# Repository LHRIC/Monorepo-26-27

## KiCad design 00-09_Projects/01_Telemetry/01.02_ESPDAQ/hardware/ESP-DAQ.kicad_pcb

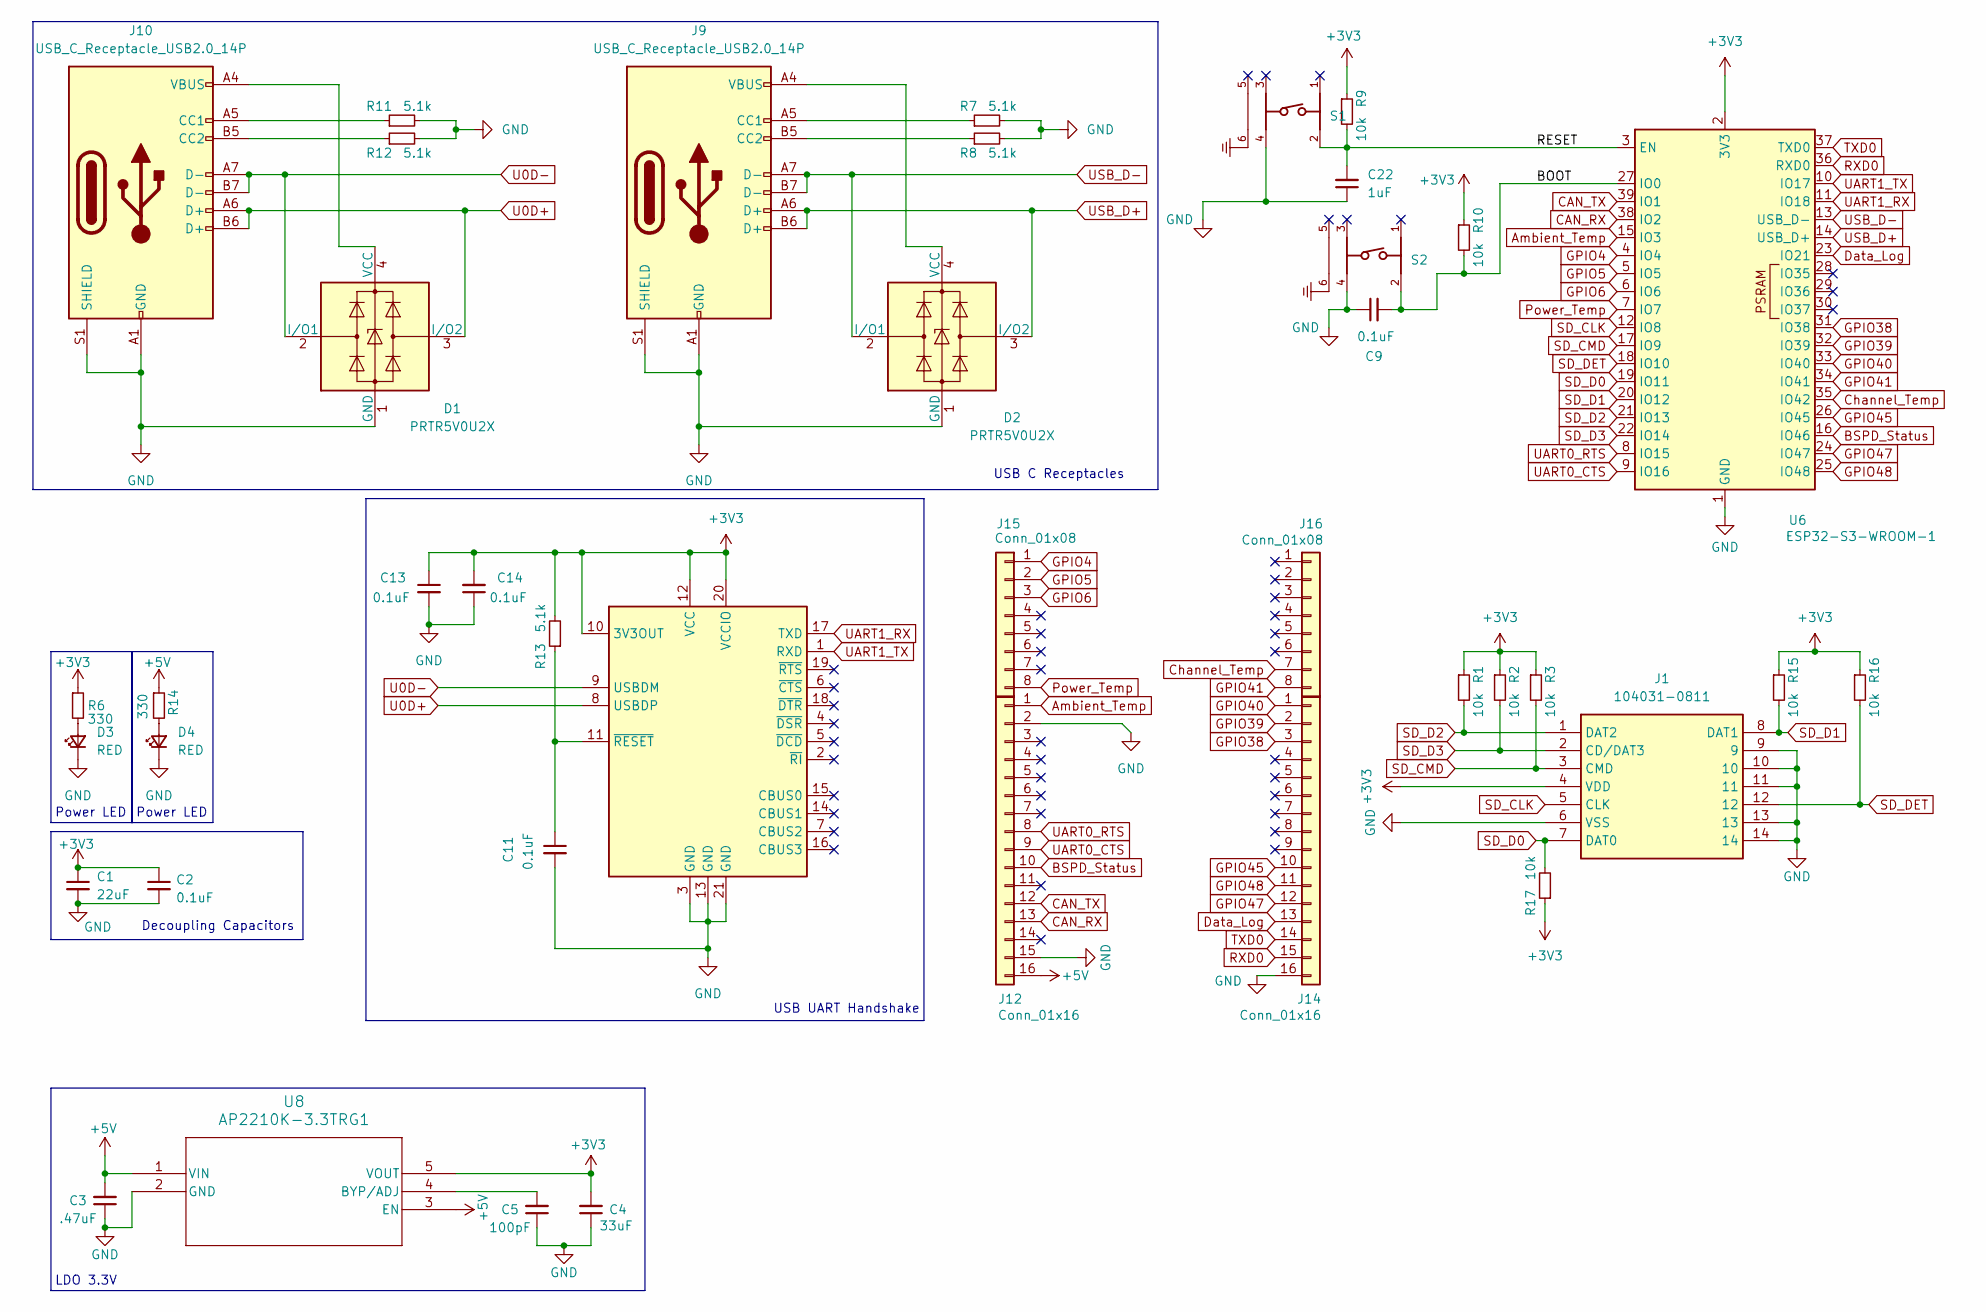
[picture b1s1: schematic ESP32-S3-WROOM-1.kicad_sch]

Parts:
C1: 22uF; C_0805_2012Metric
C2, C9, C11, C13, C14: 0.1uF; C_0603_1608Metric
C3: .47uF; C_0603_1608Metric
C4: 33uF; C_0805_2012Metric
C5: 100pF; C_0603_1608Metric
C22: 1uF; C_0603_1608Metric
D1, D2: PRTR5V0U2X; SOT-143
D3, D4: RED; LED_0603_1608Metric
J1: 104031-0811; Molex MicroSD Card 1040310811; Mouser Part Number 538-104031-0811
J9, J10: USB_C_Receptacle_USB2.0_14P; USB_C_Receptacle_XKB_U262-16XN-4BVC11
J12, J14: Conn_01x16; PinHeader_1x16_P2.54mm_Vertical
J15: Conn_01x08; 01x08 2.54mm Connector Surface Mount Right Angle Left
J16: Conn_01x08; 01x08 2.54mm Connector Surface Mount Right Angle Right
R1, R2, R3, R9, R10, R15, R16, R17: 10k; R_0603_1608Metric
R6, R14: 330; R_0603_1608Metric
R7, R8, R11, R12, R13: 5.1k; R_0603_1608Metric
S1, S2: 435171014816; SMT Switch 435171014816; DigiKey_Part_Number 732-435171014816CT-ND
U1: FT231XQ; QFN-20-1EP_4x4mm_P0.5mm_EP2.5x2.5mm
U6: ESP32-S3-WROOM-1; ESP32S3-WROOM-1U-N16R8
U8: AP2210K-3.3TRG1; SOT-23-5_DIO

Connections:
+3V3: C1.1, C2.1, C4.2, C13.1, C14.2, J1.4 (VDD), R1.1, R2.1, R3.1, R6.1, R9.1, R10.1, R13.2, R15.1, R16.1, R17.1, U1.10 (3V3OUT), U1.12 (VCC), U1.20 (VCCIO), U6.2 (3V3), U8.5 (VOUT)
+5V: C3.2, J12.16, R14.1, U8.1 (VIN), U8.3 (EN)
/BOOT: C9.2, R10.2, S2.2, U6.27 (IO0)
/RESET: C22.2, R9.2, S1.2, U6.3 (EN)
Ambient_Temp: J12.1, U6.15 (IO3)
BSPD_Status: J12.10, U6.16 (IO46)
CAN_RX: J12.13, U6.38 (IO2)
CAN_TX: J12.12, U6.39 (IO1)
Channel_Temp: J16.7, U6.35 (IO42)
Data_Log: J14.13, U6.23 (IO21)
GND: C1.2, C2.2, C3.1, C4.1, C5.1, C9.1, C11.2, C13.2, C14.1, C22.1, D1.1 (GND), D2.1 (GND), D3.1 (K), D4.1 (K), J1.6 (VSS), J1.9, J1.10, J1.11, J1.13, J1.14, J9.A1 (GND), J9.A12 (GND), J9.B1 (GND), J9.B12 (GND), J9.S1 (SHIELD), J10.A1 (GND), J10.A12 (GND), J10.B1 (GND), J10.B12 (GND), J10.S1 (SHIELD), J12.2, J12.15, J14.16, R7.2, R8.2, R11.2, R12.2, S1.4, S2.4, U1.3 (GND), U1.13 (GND), U1.21 (GND), U6.1 (GND), U6.40 (GND), U6.41 (GND), U8.2 (GND)
GPIO4: J15.1, U6.4 (IO4)
GPIO5: J15.2, U6.5 (IO5)
GPIO6: J15.3, U6.6 (IO6)
GPIO38: J14.3, U6.31 (IO38)
GPIO39: J14.2, U6.32 (IO39)
GPIO40: J14.1, U6.33 (IO40)
GPIO41: J16.8, U6.34 (IO41)
GPIO45: J14.10, U6.26 (IO45)
GPIO47: J14.12, U6.24 (IO47)
GPIO48: J14.11, U6.25 (IO48)
unnamed: D1.4 (VCC), J10.A4 (VBUS), J10.A9 (VBUS), J10.B4 (VBUS), J10.B9 (VBUS)
unnamed: D2.4 (VCC), J9.A4 (VBUS), J9.A9 (VBUS), J9.B4 (VBUS), J9.B9 (VBUS)
unnamed: D3.2 (A), R6.2
unnamed: D4.2 (A), R14.2
unnamed: J9.A5 (CC1), R7.1
unnamed: J9.B5 (CC2), R8.1
unnamed: J10.A5 (CC1), R11.1
unnamed: J10.B5 (CC2), R12.1
unnamed: C11.1, R13.1, U1.11 (~RESET)
unnamed: C5.2, U8.4 (BYP/ADJ)
Power_Temp: J15.8, U6.7 (IO7)
RXD0: J14.15, U6.36 (RXD0)
SD_CLK: J1.5 (CLK), U6.12 (IO8)
SD_CMD: J1.3 (CMD), R3.2, U6.17 (IO9)
SD_D0: J1.7 (DAT0), R17.2, U6.19 (IO11)
SD_D1: J1.8 (DAT1), R15.2, U6.20 (IO12)
SD_D2: J1.1 (DAT2), R1.2, U6.21 (IO13)
SD_D3: J1.2 (CD/DAT3), R2.2, U6.22 (IO14)
SD_DET: J1.12, R16.2, U6.18 (IO10)
TXD0: J14.14, U6.37 (TXD0)
U0D+: D1.3 (I/O2), J10.A6 (D+), J10.B6 (D+), U1.8 (USBDP)
U0D-: D1.2 (I/O1), J10.A7 (D-), J10.B7 (D-), U1.9 (USBDM)
UART0_CTS: J12.9, U6.9 (IO16)
UART0_RTS: J12.8, U6.8 (IO15)
UART1_RX: U1.17 (TXD), U6.11 (IO18)
UART1_TX: U1.1 (RXD), U6.10 (IO17)
USB_D+: D2.3 (I/O2), J9.A6 (D+), J9.B6 (D+), U6.14 (USB_D+)
USB_D-: D2.2 (I/O1), J9.A7 (D-), J9.B7 (D-), U6.13 (USB_D-)

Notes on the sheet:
USB C Receptacles
Power LED
LDO 3.3V
USB UART Handshake
Decoupling Capacitors

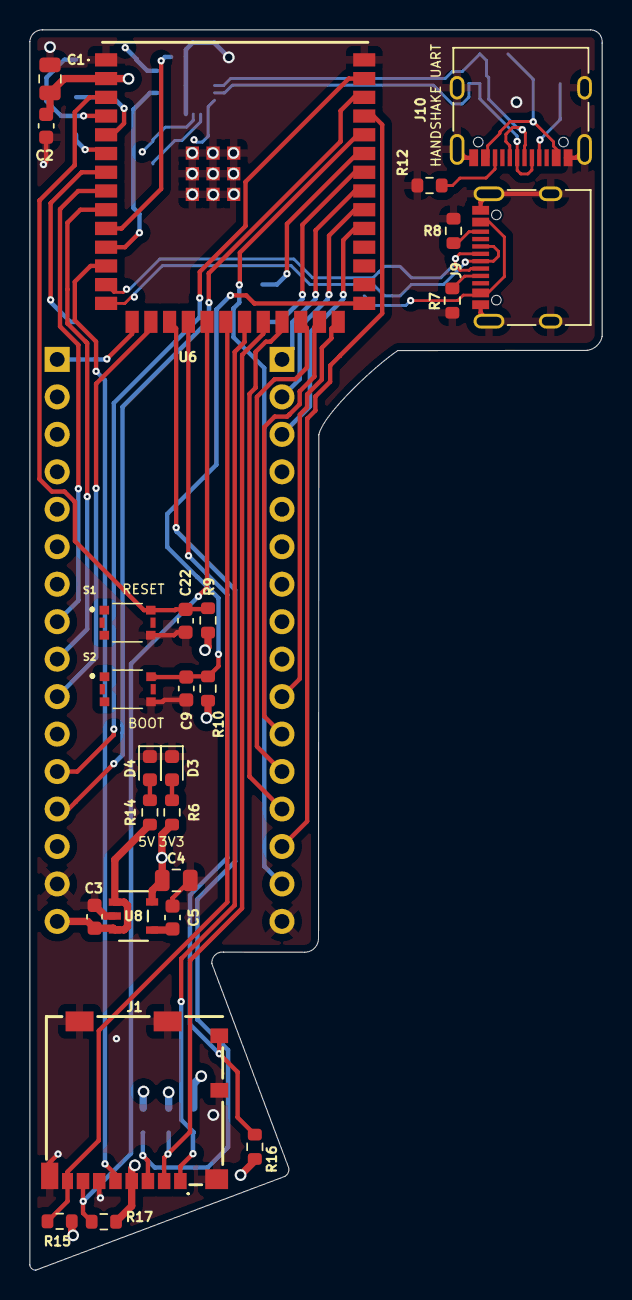
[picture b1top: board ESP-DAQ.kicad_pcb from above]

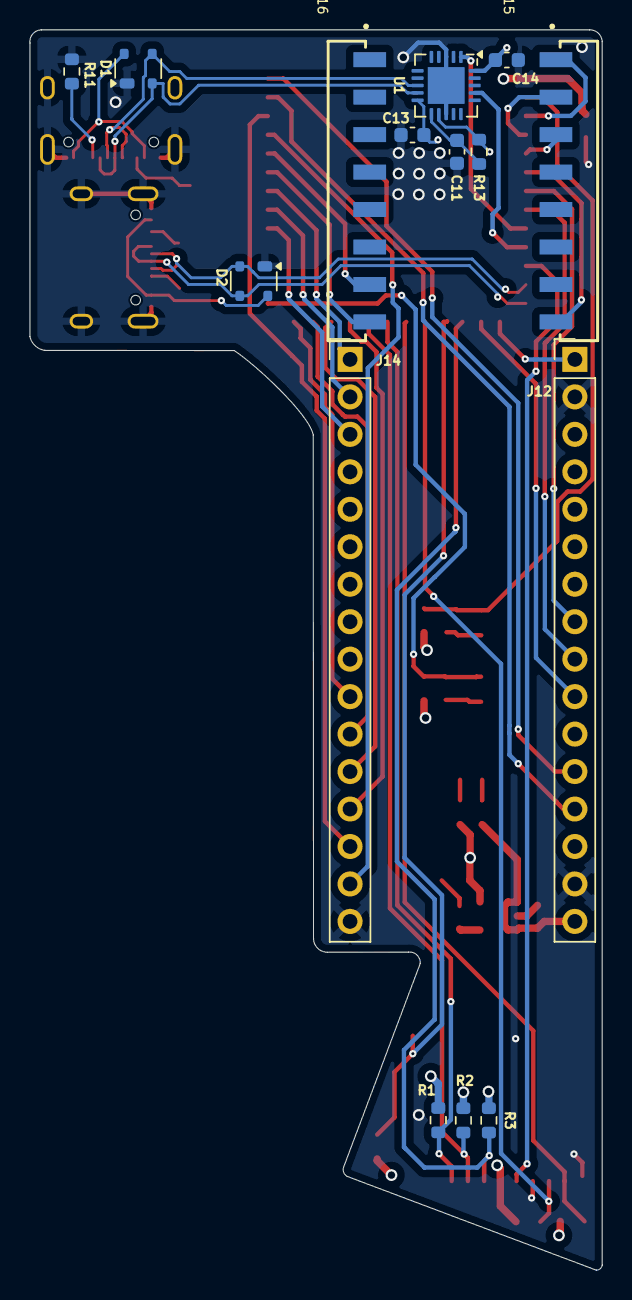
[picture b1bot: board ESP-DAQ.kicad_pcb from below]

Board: 4 copper layers, 38.8 x 84.1 mm, 41 parts (15 on the bottom side), 49 nets.

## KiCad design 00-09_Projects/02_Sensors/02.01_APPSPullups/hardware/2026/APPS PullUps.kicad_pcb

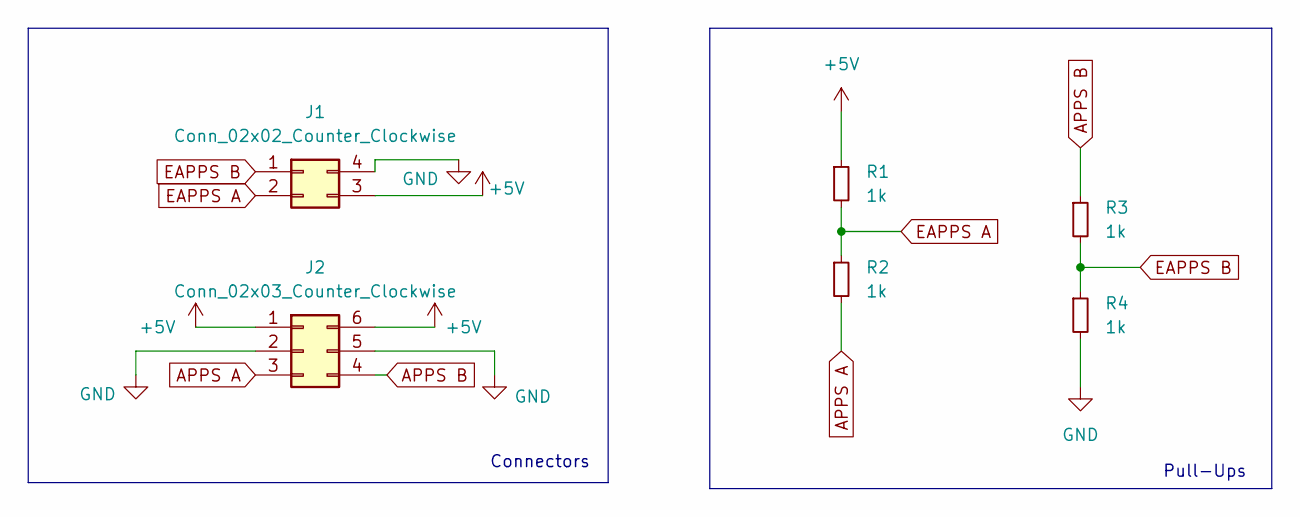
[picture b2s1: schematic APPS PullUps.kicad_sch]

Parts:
J1: Conn_02x02_Counter_Clockwise; ATM13-4P-BMxx
J2: Conn_02x03_Counter_Clockwise; ATM13-6P-BMxx
R1, R2, R3, R4: 1k; R_0603_1608Metric

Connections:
+5V: J1.3, J2.1, J2.6, R1.1
APPS A: J2.3, R2.2
APPS B: J2.4, R3.1
EAPPS A: J1.2, R1.2, R2.1
EAPPS B: J1.1, R3.2, R4.1
GND: J1.4, J2.2, J2.5, R4.2

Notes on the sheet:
Pull-Ups
Connectors

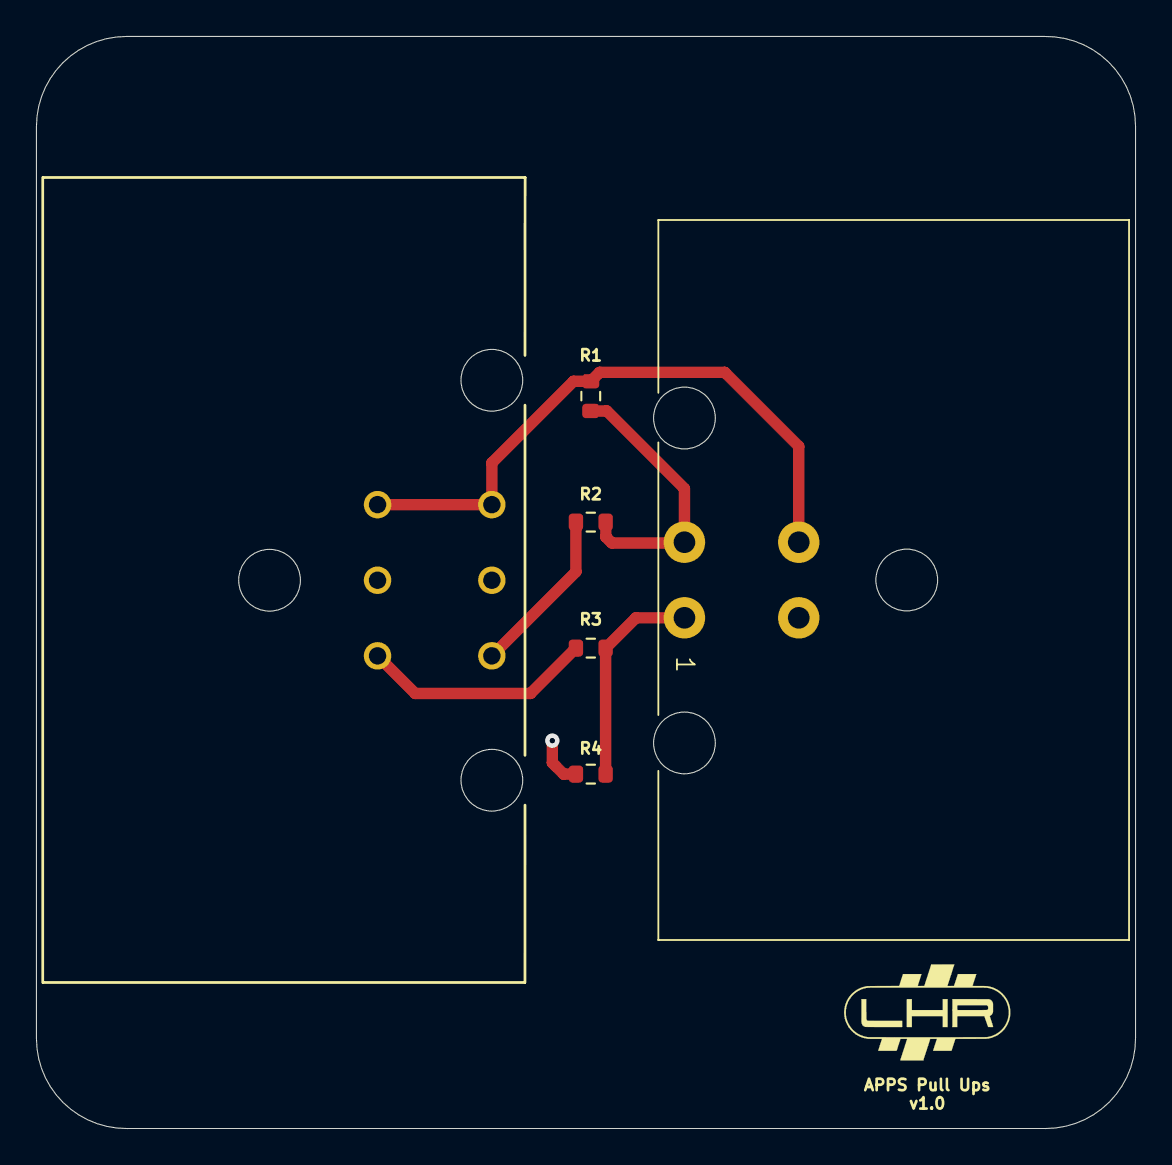
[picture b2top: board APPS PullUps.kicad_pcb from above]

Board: 2 copper layers, 61.1 x 60.7 mm, 6 parts (0 on the bottom side), 6 nets.

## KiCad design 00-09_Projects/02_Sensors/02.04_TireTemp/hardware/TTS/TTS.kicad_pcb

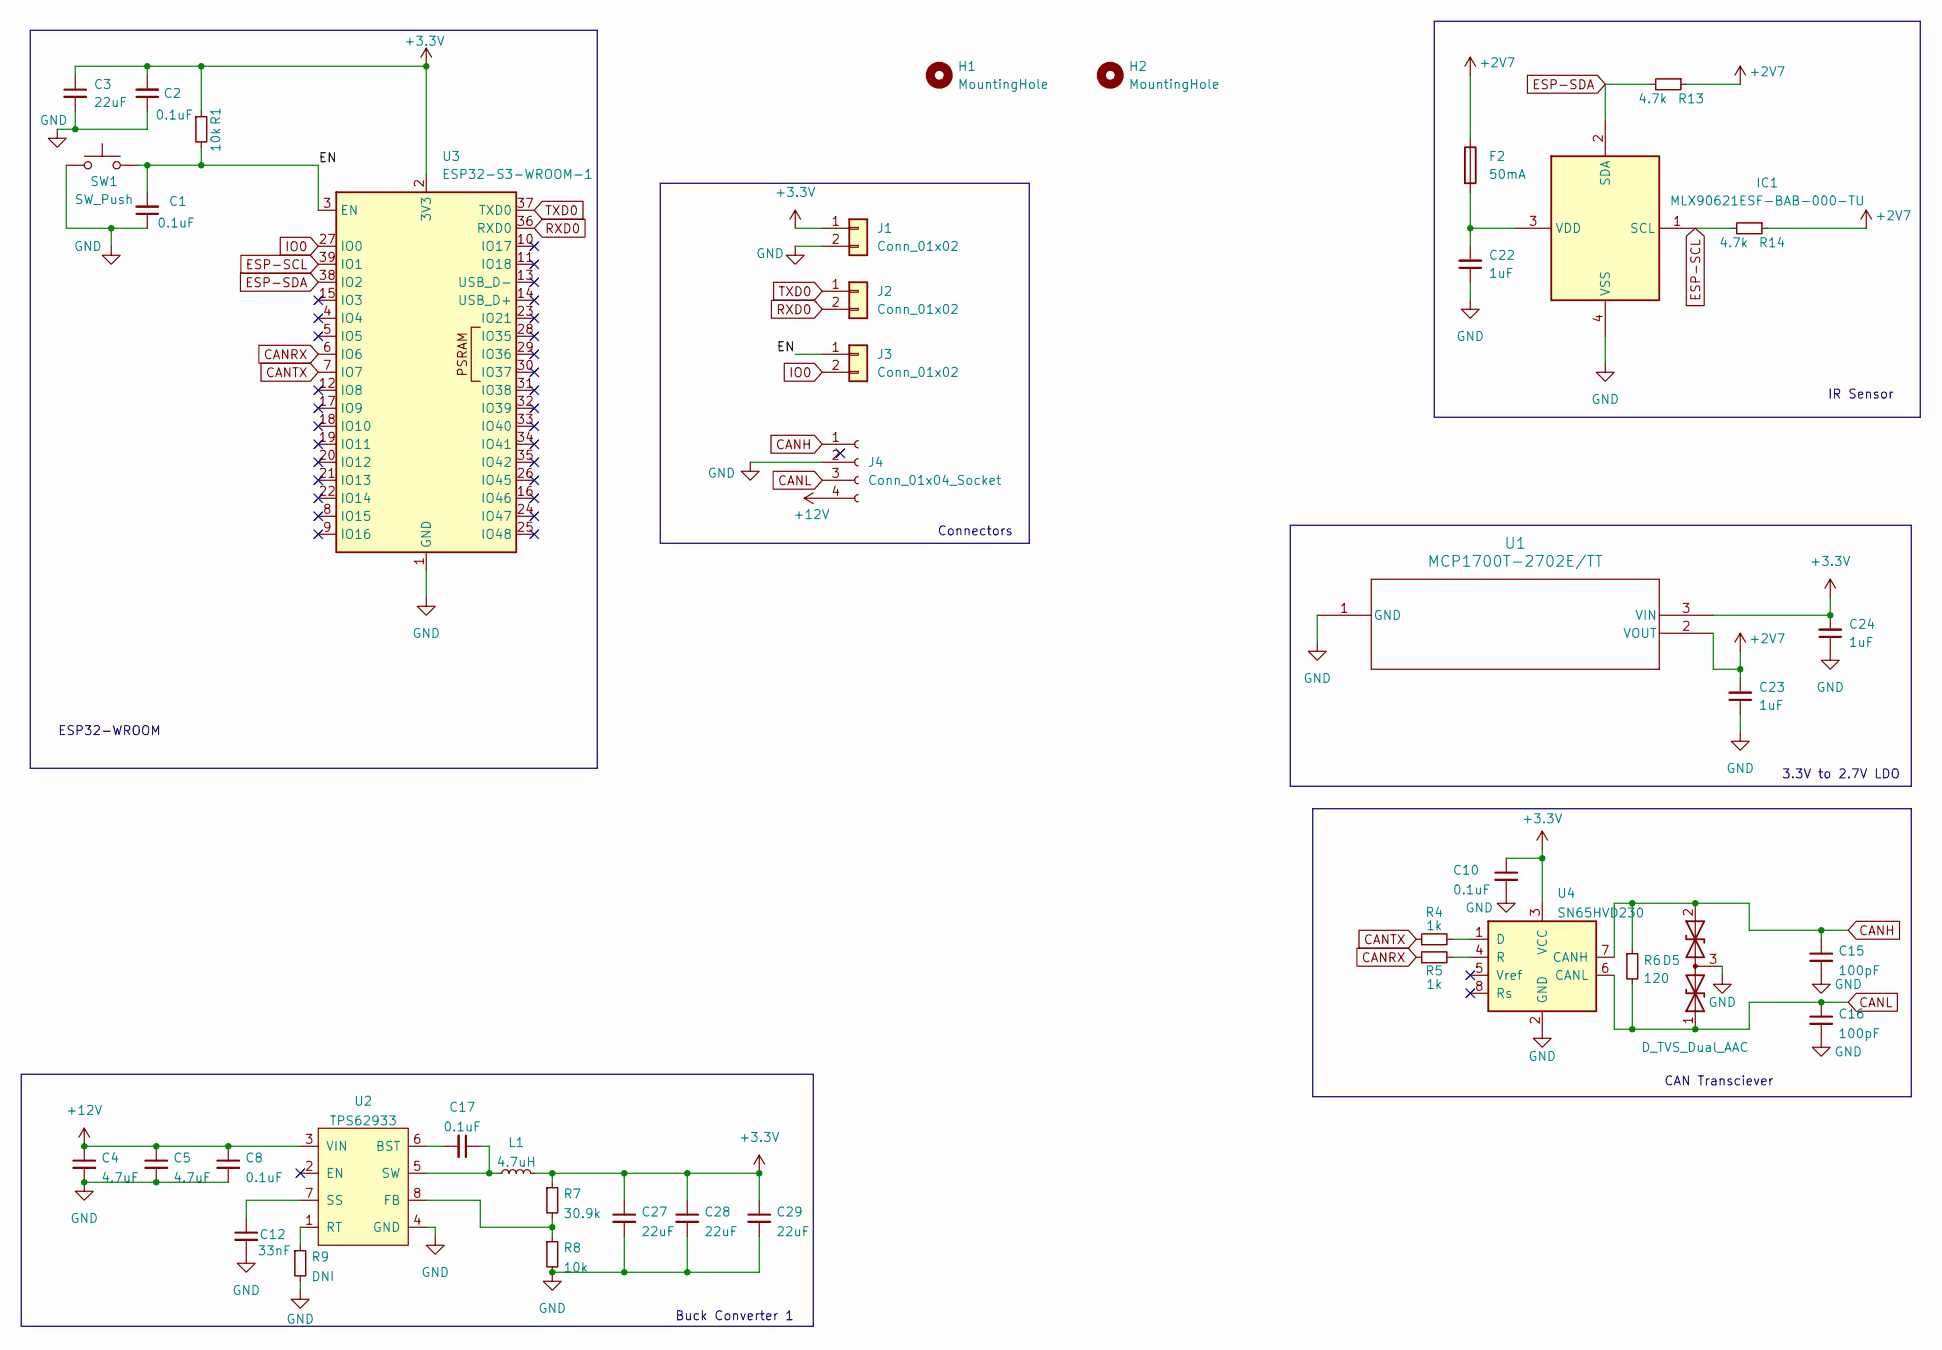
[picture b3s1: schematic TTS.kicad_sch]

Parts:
C1, C2, C8, C10, C17: 0.1uF; C_0603_1608Metric
C3, C27, C28, C29: 22uF; C_0805_2012Metric
C4, C5: 4.7uF; C_0805_2012Metric
C12: 33nF; C_0603_1608Metric
C15, C16: 100pF; C_0603_1608Metric
C22, C23, C24: 1uF; C_0603_1608Metric
D5: D_TVS_Dual_AAC; SOT-23
F2: 50mA; Fuse_0603_1608Metric
H1, H2: MountingHole; MountingHole_3.2mm_M3
IC1: MLX90621ESF-BAB-000-TU; MLX90621ESFBAB000TU; Mouser Part Number 482-90621ESFBAB000TU
J1, J2, J3: Conn_01x02; PinHeader_1x02_P2.54mm_Vertical
J4: Conn_01x04_Socket; Molex_Micro-Fit_3.0_43045-0400_2x02_P3.00mm_Horizontal
L1: 4.7uH; SRU8043-4R7Y
R1, R8: 10k; R_0603_1608Metric
R4, R5: 1k; R_0603_1608Metric
R6: 120; R_0603_1608Metric
R7: 30.9k; R_0603_1608Metric
R9: DNI; R_0603_1608Metric
R13, R14: 4.7k; R_0603_1608Metric
SW1: SW_Push; SW_Push_1P1T_NO_CK_KMR2
U1: MCP1700T-2702E/TT; SOT-23_MC_MCH
U2: TPS62933; SOT-583
U3: ESP32-S3-WROOM-1
U4: SN65HVD230; SOIC-8_3.9x4.9mm_P1.27mm

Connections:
+2V7: C23.2, F2.1, R13.1, R14.1, U1.2 (VOUT)
+3.3V: C2.2, C3.1, C10.1, C24.2, C27.1, C28.1, C29.1, J1.1, L1.2, R1.1, R7.1, U1.3 (VIN), U3.2 (3V3), U4.3 (VCC)
+12V: C4.1, C5.1, C8.1, J4.4, U2.3 (VIN)
/EN: C1.2, J3.1, R1.2, SW1.2, U3.3 (EN)
CANH: C15.1, D5.2 (A2), J4.1, R6.1, U4.7 (CANH)
CANL: C16.1, D5.1 (A1), J4.3, R6.2, U4.6 (CANL)
CANRX: R5.1, U3.6 (IO6)
CANTX: R4.1, U3.7 (IO7)
ESP-SCL: IC1.1 (SCL), R14.2, U3.39 (IO1)
ESP-SDA: IC1.2 (SDA), R13.2, U3.38 (IO2)
GND: C1.1, C2.1, C3.2, C4.2, C5.2, C8.2, C10.2, C12.2, C15.2, C16.2, C22.1, C23.1, C24.1, C27.2, C28.2, C29.2, D5.3 (common), IC1.4 (VSS), J1.2, J4.2, R8.2, R9.2, SW1.1, U1.1 (GND), U2.4 (GND), U3.1 (GND), U3.40 (GND), U3.41 (GND), U4.2 (GND)
IO0: J3.2, U3.27 (IO0)
unnamed: C22.2, F2.2, IC1.3 (VDD)
unnamed: C17.2, U2.6 (BST)
unnamed: R7.2, R8.1, U2.8 (FB)
unnamed: R9.1, U2.1 (RT)
unnamed: C12.1, U2.7 (SS)
unnamed: C17.1, L1.1, U2.5 (SW)
unnamed: R4.2, U4.1 (D)
unnamed: R5.2, U4.4 (R)
RXD0: J2.2, U3.36 (RXD0)
TXD0: J2.1, U3.37 (TXD0)

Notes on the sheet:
3.3V to 2.7V LDO
Buck Converter 1
CAN Transciever
ESP32-WROOM
IR Sensor
Connectors

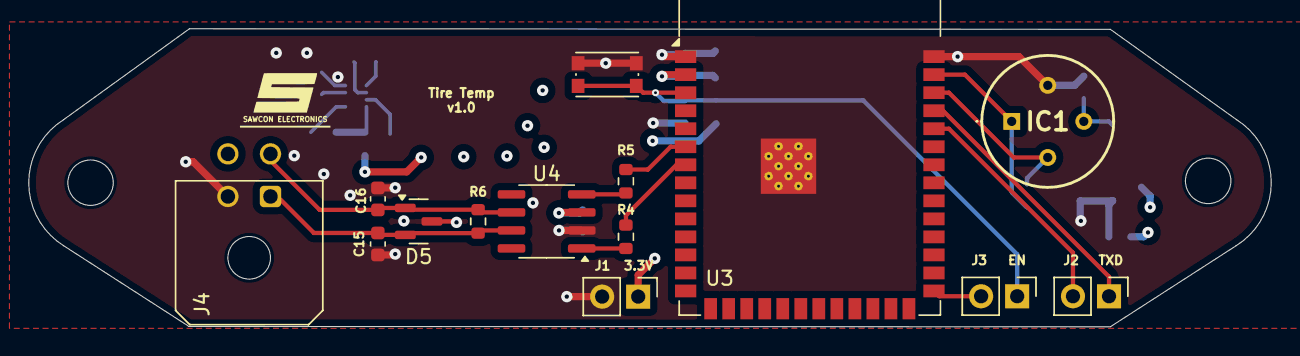
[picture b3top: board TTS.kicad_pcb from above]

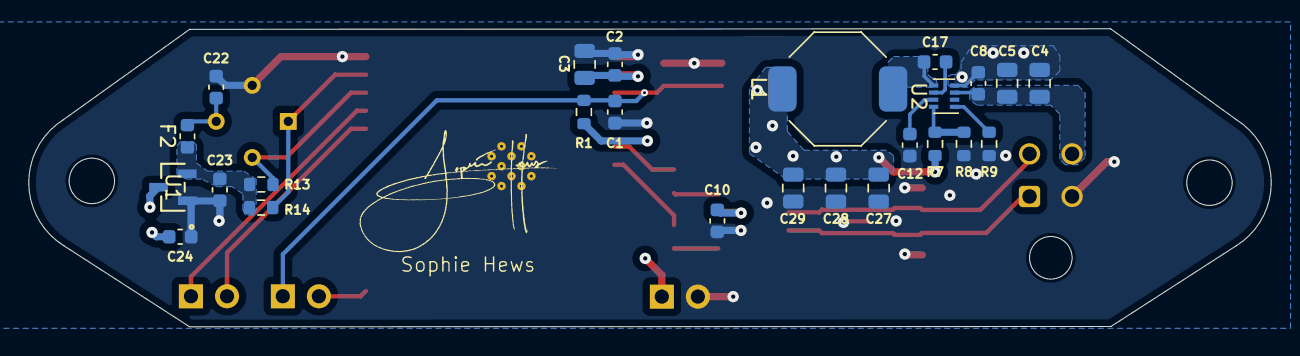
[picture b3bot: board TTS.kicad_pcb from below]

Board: 4 copper layers, 87.5 x 21.0 mm, 41 parts (25 on the bottom side), 22 nets.

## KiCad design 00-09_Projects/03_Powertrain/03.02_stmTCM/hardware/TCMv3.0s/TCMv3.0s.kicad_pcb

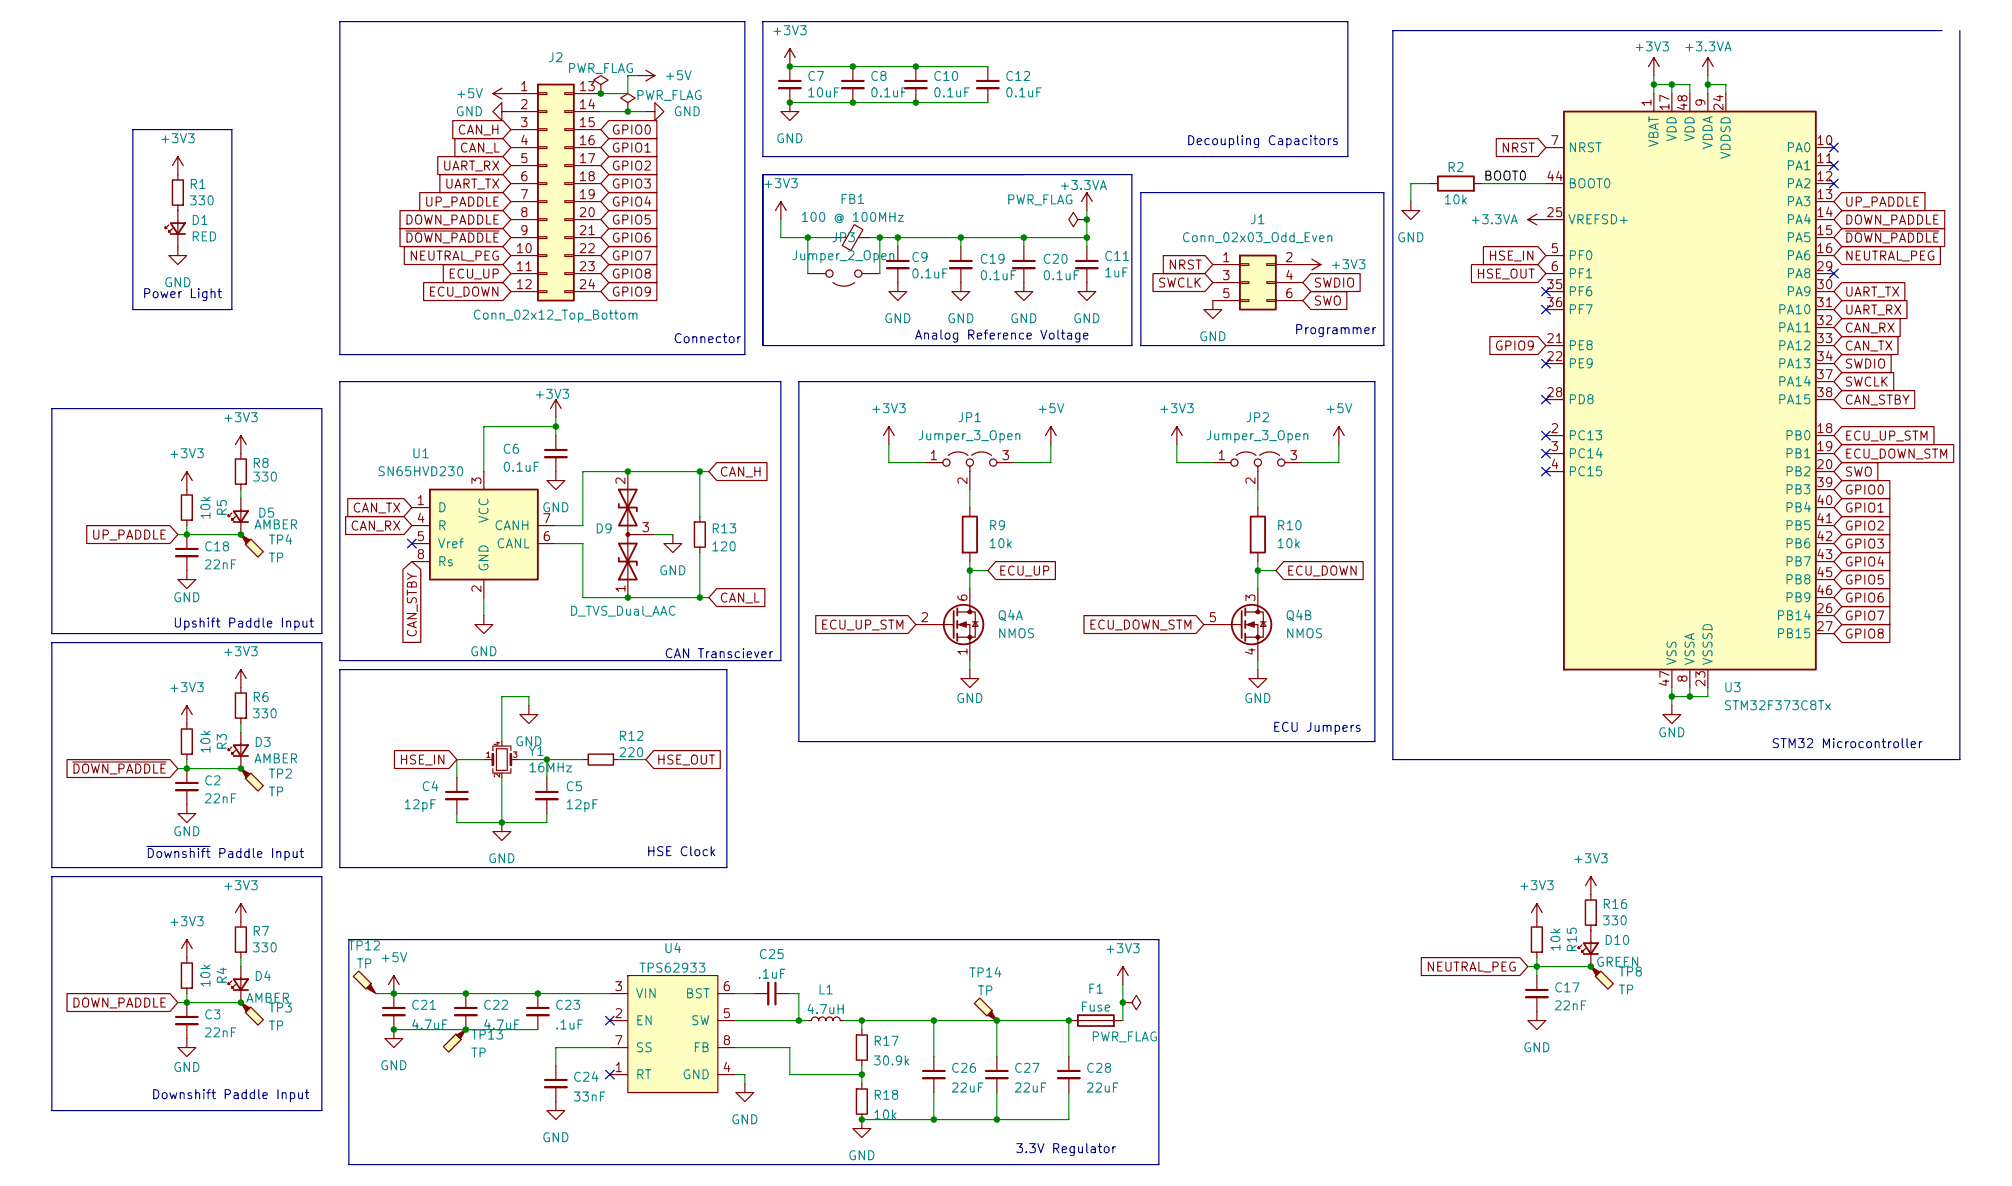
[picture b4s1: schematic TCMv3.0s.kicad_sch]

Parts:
C2, C3, C17, C18: 22nF; C_0603_1608Metric
C4, C5: 12pF; C_0402_1005Metric
C6, C8, C9, C10, C12, C19, C20: 0.1uF; C_0603_1608Metric
C7: 10uF; C_0805_2012Metric
C11: 1uF; C_0603_1608Metric
C21, C22: 4.7uF; C_0805_2012Metric
C23, C25: .1uF; C_0603_1608Metric
C24: 33nF; C_0603_1608Metric
C26, C27, C28: 22uF; C_0805_2012Metric
D1: RED; LED_0603_1608Metric
D3, D4, D5: AMBER; LED_0603_1608Metric
D9: D_TVS_Dual_AAC; SOT-23
D10: GREEN; LED_0603_1608Metric
F1: Fuse; Fuse_1206_3216Metric
FB1: 100 @ 100MHz; C_0402_1005Metric
J1: Conn_02x03_Odd_Even; Molex_Micro-Fit_3.0_43045-0612_2x03_P3.00mm_Vertical
J2: Conn_02x12_Top_Bottom; AMPHENOL_PCB_24P
JP1, JP2: Jumper_3_Open; SolderJumper-3_P1.3mm_Open_RoundedPad1.0x1.5mm
JP3: Jumper_2_Open; SolderJumper-2_P1.3mm_Open_RoundedPad1.0x1.5mm
L1: 4.7uH; SRU8043-4R7Y
Q4: NMOS; SOT-363_SC-70-6
R1, R6, R7, R8, R16: 330; R_0603_1608Metric
R2, R3, R4, R5, R9, R10, R15, R18: 10k; R_0603_1608Metric
R12: 220; R_0603_1608Metric
R13: 120; R_0603_1608Metric
R17: 30.9k; R_0603_1608Metric
TP2, TP3, TP4, TP8, TP12, TP13, TP14: TP; TestPoint_Pad_D2.0mm
U1: SN65HVD230; SOIC-8_3.9x4.9mm_P1.27mm
U3: STM32F373C8Tx; LQFP-48_7x7mm_P0.5mm
U4: TPS62933; SOT-583
Y1: 16MHz; Crystal_SMD_3225-4Pin_3.2x2.5mm

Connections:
+3.3VA: C9.1, C11.1, C19.1, C20.1, FB1.2, JP3.1 (A), U3.9 (VDDA), U3.24 (VDDSD), U3.25 (VREFSD+)
+3V3: C6.1, C7.1, C8.1, C10.1, C12.1, F1.2, FB1.1, J1.2, JP1.1 (A), JP2.1 (A), JP3.2 (B), R1.2, R3.2, R4.2, R5.2, R6.2, R7.2, R8.2, R15.2, R16.2, U1.3 (VCC), U3.1 (VBAT), U3.17 (VDD), U3.48 (VDD)
+5V: C21.1, C22.1, C23.1, J2.1, J2.13, JP1.3 (B), JP2.3 (B), TP12.1, U4.3 (VIN)
/BOOT0: R2.2, U3.44 (BOOT0)
CAN_H: D9.2 (A2), J2.3, R13.1, U1.7 (CANH)
CAN_L: D9.1 (A1), J2.4, R13.2, U1.6 (CANL)
CAN_RX: U1.4 (R), U3.32 (PA11)
CAN_STBY: U1.8 (Rs), U3.38 (PA15)
CAN_TX: U1.1 (D), U3.33 (PA12)
DOWN_PADDLE: C3.1, D4.1 (K), J2.8, R4.1, TP3.1, U3.14 (PA4)
ECU_DOWN: J2.12, Q4.3 (D), R10.2
ECU_DOWN_STM: Q4.5 (G), U3.19 (PB1)
ECU_UP: J2.11, Q4.6 (D), R9.2
ECU_UP_STM: Q4.2 (G), U3.18 (PB0)
GND: C2.2, C3.2, C4.2, C5.2, C6.2, C7.2, C8.2, C9.2, C10.2, C11.2, C12.2, C17.2, C18.2, C19.2, C20.2, C21.2, C22.2, C23.2, C24.2, C26.2, C27.2, C28.2, D1.1 (K), D9.3 (common), J1.5, J2.2, J2.14, Q4.1 (S), Q4.4 (S), R2.1, R18.2, TP13.1, U1.2 (GND), U3.8 (VSSA), U3.23 (VSSSD), U3.47 (VSS), U4.4 (GND), Y1.2, Y1.4
GPIO0: J2.15, U3.39 (PB3)
GPIO1: J2.16, U3.40 (PB4)
GPIO2: J2.17, U3.41 (PB5)
GPIO3: J2.18, U3.42 (PB6)
GPIO4: J2.19, U3.43 (PB7)
GPIO5: J2.20, U3.45 (PB8)
GPIO6: J2.21, U3.46 (PB9)
GPIO7: J2.22, U3.26 (PB14)
GPIO8: J2.23, U3.27 (PB15)
GPIO9: J2.24, U3.21 (PE8)
HSE_IN: C4.1, U3.5 (PF0), Y1.1
HSE_OUT: R12.1, U3.6 (PF1)
NEUTRAL_PEG: C17.1, D10.1 (K), J2.10, R15.1, TP8.1, U3.16 (PA6)
NRST: J1.1, U3.7 (NRST)
unnamed: C5.1, R12.2, Y1.3
unnamed: C26.1, C27.1, C28.1, F1.1, L1.2, R17.1, TP14.1
unnamed: D1.2 (A), R1.1
unnamed: D3.2 (A), R6.1
unnamed: D4.2 (A), R7.1
unnamed: D5.2 (A), R8.1
unnamed: D10.2 (A), R16.1
unnamed: JP1.2 (C), R9.1
unnamed: JP2.2 (C), R10.1
unnamed: C25.2, U4.6 (BST)
unnamed: R17.2, R18.1, U4.8 (FB)
unnamed: C24.1, U4.7 (SS)
unnamed: C25.1, L1.1, U4.5 (SW)
SWCLK: J1.3, U3.37 (PA14)
SWDIO: J1.4, U3.34 (PA13)
SWO: J1.6, U3.20 (PB2)
UART_RX: J2.5, U3.31 (PA10)
UART_TX: J2.6, U3.30 (PA9)
UP_PADDLE: C18.1, D5.1 (K), J2.7, R5.1, TP4.1, U3.13 (PA3)
~DOWN_PADDLE: C2.1, D3.1 (K), J2.9, R3.1, TP2.1, U3.15 (PA5)

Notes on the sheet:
Analog Reference Voltage
~{Downshift} Paddle Input
CAN Transciever
Programmer
ECU Jumpers
Connector
Power Light
Downshift Paddle Input
3.3V Regulator
Decoupling Capacitors
HSE Clock
STM32 Microcontroller
Upshift Paddle Input

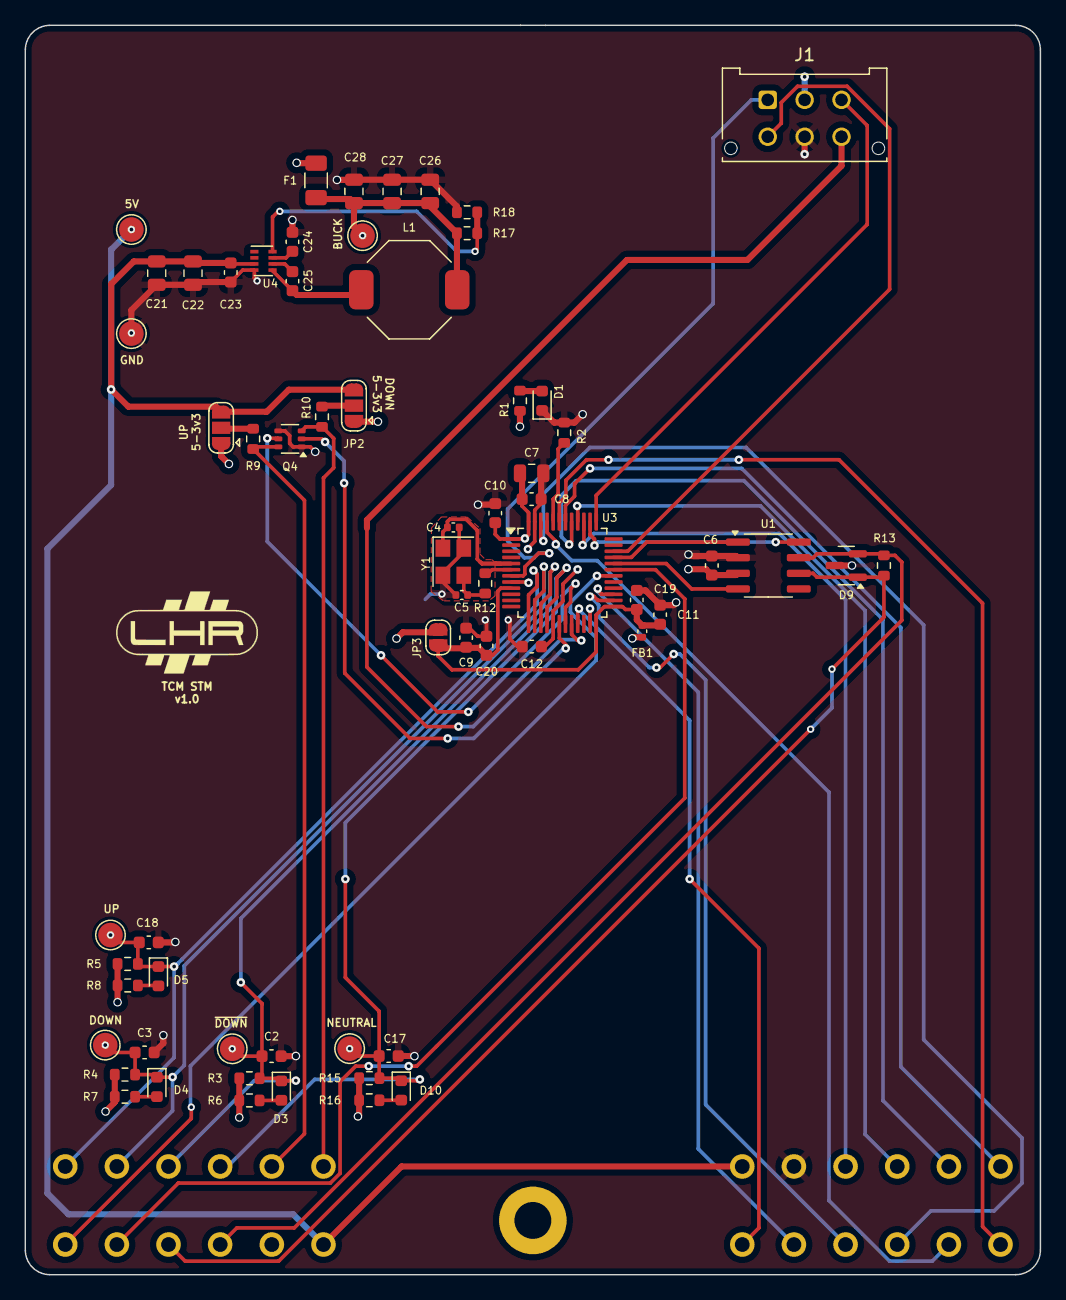
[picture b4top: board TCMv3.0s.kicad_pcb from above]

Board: 4 copper layers, 82.5 x 101.6 mm, 65 parts (0 on the bottom side), 49 nets.

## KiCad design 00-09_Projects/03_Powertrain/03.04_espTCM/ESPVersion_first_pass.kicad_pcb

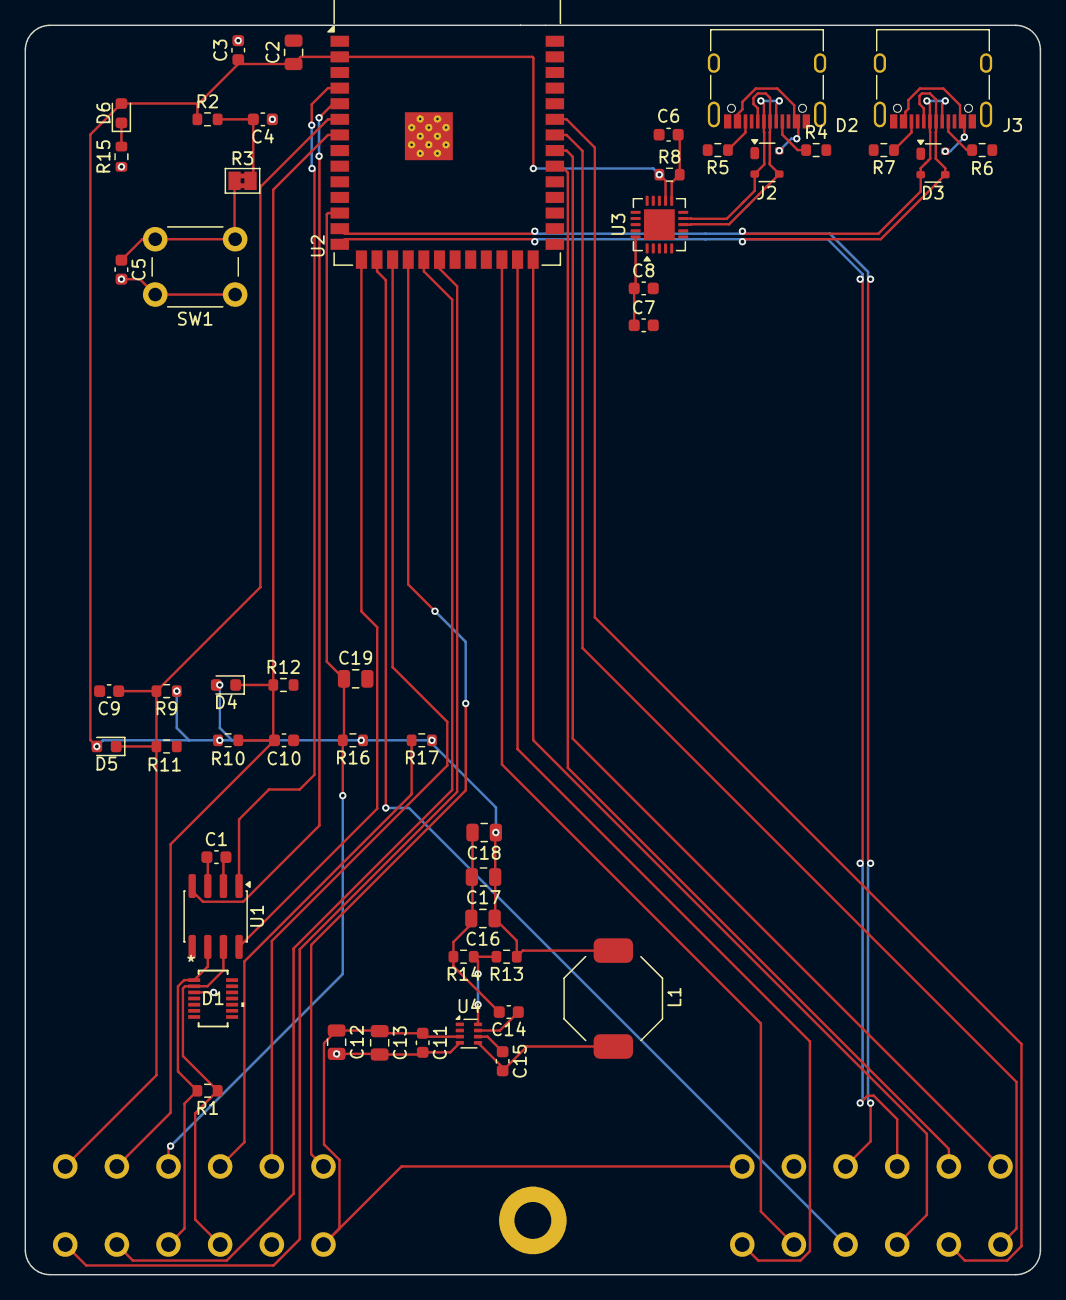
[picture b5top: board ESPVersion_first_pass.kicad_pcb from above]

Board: 2 copper layers, 82.6 x 101.6 mm, 51 parts (0 on the bottom side), 44 nets.

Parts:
C1, C3, C5, C6, C7, C8, C11, C15: 0.1uF; C_0603_1608Metric
C2, C16, C17, C18: 22uF; C_0805_2012Metric
C4: 1uF; C_0603_1608Metric
C9, C10: 22nF; C_0603_1608Metric
C12, C13: 4.7uF; C_0805_2012Metric
C14: 33uF; C_0603_1608Metric
C19: 22nF; C_0805_2012Metric
D1: D_TVS_Dual_AAC; SOT-23-THIN-14_DYY_TEX
D2, D3: PRTR5V0U2X; SOT-143
D4, D5, D6: LED; LED_0603_1608Metric
J1: Conn_02x12_Top_Bottom; AMPHENOL_PCB_24P
J2, J3: USB_C_Receptacle_USB2.0_14P; USB_C_Receptacle_XKB_U262-16XN-4BVC11
L1: 4.7uH; SRU8043-4R7Y
R1: 120; R_0603_1608Metric
R2, R9, R10, R14, R16, R17: 10k; R_0603_1608Metric
R3: 0; SolderJumper-2_P1.3mm_Bridged2Bar_Pad1.0x1.5mm
R4, R5, R6, R7, R8: 5.1k; R_0603_1608Metric
R11, R12, R15: 330; R_0603_1608Metric
R13: 30.9k; R_0603_1608Metric
SW1: SW_Push; SW_PUSH_6mm
U1: SN65HVD230; SOIC-8_3.9x4.9mm_P1.27mm
U2: ESP32-S3-WROOM-1
U3: FT231XQ; QFN-20-1EP_4x4mm_P0.5mm_EP2.5x2.5mm
U4: TPS62933; SOT-583-8

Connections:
+3V3: C1.1, C2.1, C3.1, C7.1, C8.1, C16.1, C17.1, C18.1, D4.2 (A), D5.2 (A), D6.2 (A), L1.2, R2.1, R8.1, R9.1, R10.1, R13.1, R16.1, R17.1, U1.3 (VCC), U2.2 (3V3), U3.10 (3V3OUT), U3.12 (VCC), U3.20 (VCCIO)
+5V: C11.1, C12.1, C13.1, J1.1, J1.13, U4.3 (VIN)
/EN: C4.2, R2.2, R3.2, U2.3 (EN)
CAN_H: D1.2 (A2), J1.3, R1.1, U1.7 (CANH)
CAN_L: D1.1 (A1), J1.4, R1.2, U1.6 (CANL)
CAN_RX: U1.4 (R), U2.5 (IO5)
CAN_STBY: U1.8 (Rs), U2.15 (IO3)
CAN_TX: U1.1 (D), U2.4 (IO4)
Down Paddle: C10.1, D4.1 (K), J1.8, R10.2, R12.1, U2.7 (IO7)
ECU Down: J1.12, U2.18 (IO10)
ECU Up: J1.11, U2.17 (IO9)
GND: C1.2, C2.2, C3.2, C4.1, C5.2, C6.2, C7.2, C8.2, C9.2, C10.2, C11.2, C12.2, C13.2, C14.2, C16.2, C17.2, C18.2, C19.2, D1.3 (common), D2.1 (GND), D3.1 (GND), J1.2, J1.14, J2.A1 (GND), J2.A12 (GND), J2.B1 (GND), J2.B12 (GND), J2.S1 (SHIELD), J3.A1 (GND), J3.A12 (GND), J3.B1 (GND), J3.B12 (GND), J3.S1 (SHIELD), R4.2, R5.2, R6.2, R7.2, R11.2, R12.2, R14.2, R15.1, SW1.1, U1.2 (GND), U2.1 (GND), U2.40 (GND), U2.41 (GND), U3.3 (GND), U3.13 (GND), U3.21 (GND), U4.4 (GND)
GPIO0: J1.17, U2.32 (IO39)
GPIO1: J1.18, U2.33 (IO40)
GPIO2: J1.19, U2.34 (IO41)
GPIO3: J1.20, U2.35 (IO42)
GPIO4: J1.21, U2.26 (IO45)
GPIO5: J1.22, U2.16 (IO46)
GPIO6: J1.23, U2.24 (IO47)
GPIO7: J1.24, U2.25 (IO48)
unnamed: C5.1, R3.1, SW1.2
unnamed: D2.4 (VCC), J2.A4 (VBUS), J2.A9 (VBUS), J2.B4 (VBUS), J2.B9 (VBUS)
unnamed: D3.4 (VCC), J3.A4 (VBUS), J3.A9 (VBUS), J3.B4 (VBUS), J3.B9 (VBUS)
unnamed: D6.1 (K), R15.2
unnamed: J2.A5 (CC1), R4.1
unnamed: J2.B5 (CC2), R5.1
unnamed: J3.A5 (CC1), R6.1
unnamed: J3.B5 (CC2), R7.1
unnamed: C6.1, R8.2, U3.11 (~RESET)
unnamed: C15.1, U4.6 (BST)
unnamed: R13.2, R14.1, U4.8 (FB)
unnamed: C14.1, U4.7 (SS)
unnamed: C15.2, L1.1, U4.5 (SW)
Neutral Peg: J1.10, R17.2, U2.38 (IO2)
RXD0: U2.36 (RXD0), U3.1 (RXD)
TXD0: U2.37 (TXD0), U3.17 (TXD)
U0D+: D2.3 (I/O2), J2.A6 (D+), J2.B6 (D+), U3.8 (USBDP)
U0D-: D2.2 (I/O1), J2.A7 (D-), J2.B7 (D-), U3.9 (USBDM)
UART_RX: J1.5, U2.19 (IO11)
UART_TX: J1.6, U2.20 (IO12)
USB_D+: D3.3 (I/O2), J1.16, J3.A6 (D+), J3.B6 (D+), U2.14 (USB_D+)
USB_D-: D3.2 (I/O1), J1.15, J3.A7 (D-), J3.B7 (D-), U2.13 (USB_D-)
Up Paddle: C9.1, D5.1 (K), J1.7, R9.2, R11.1, U2.6 (IO6)
~Down Paddle: C19.1, J1.9, R16.2, U2.12 (IO8)
